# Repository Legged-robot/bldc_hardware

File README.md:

# BLDC motor controller Hardware

| Eagle PCB| Mounted PCB Controller |
:-:|:-:
 |  

## Credits
Controller based on [3phase_integrated from Ben Katz](https://github.com/bgkatz/3phase_integrated)

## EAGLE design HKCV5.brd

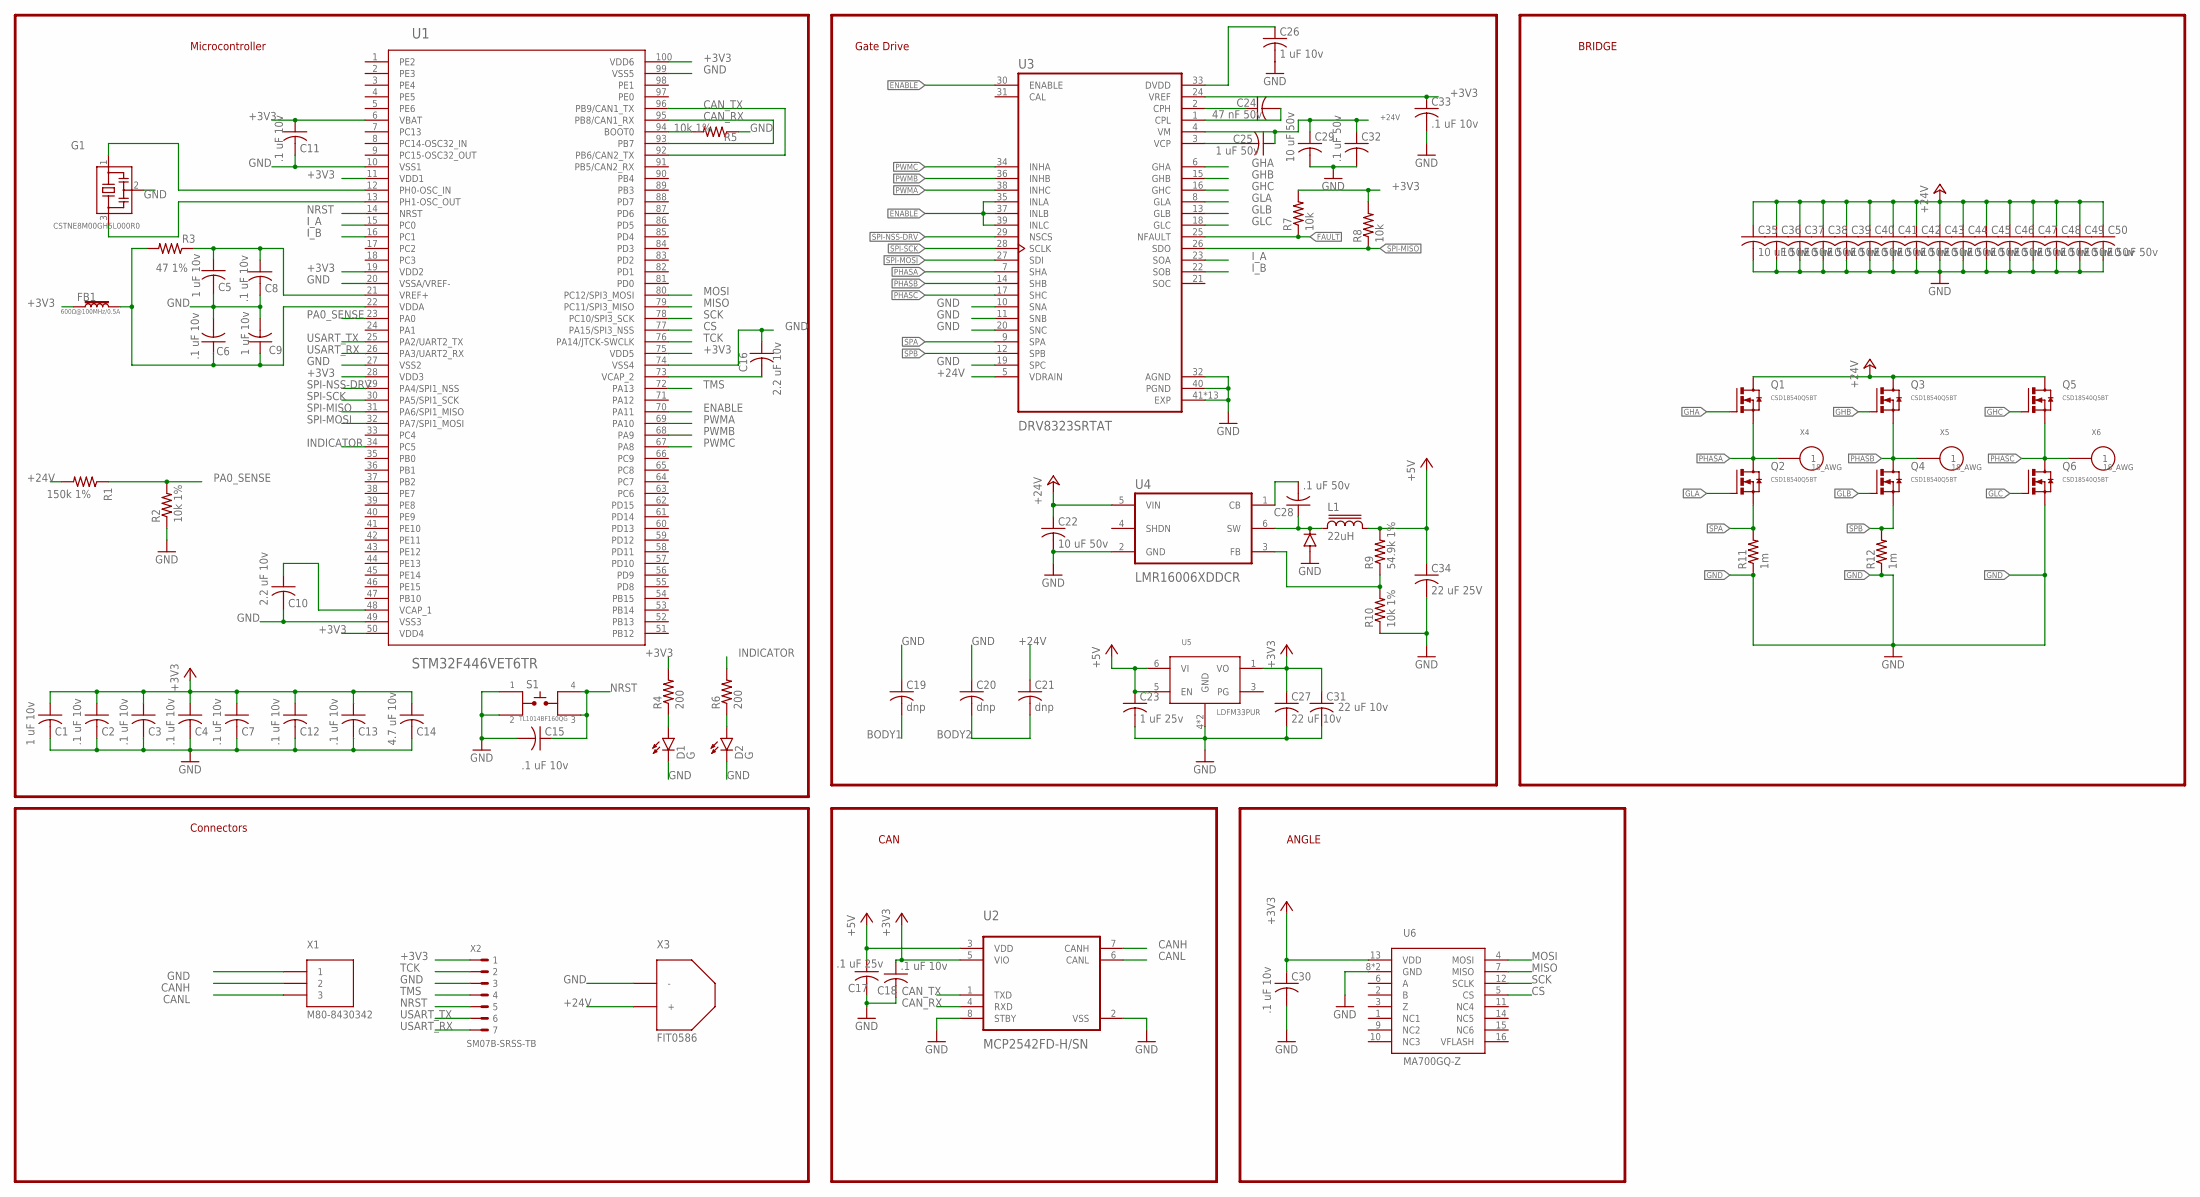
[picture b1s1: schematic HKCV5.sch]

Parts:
C1, C5, C9, C26: 1 uF 10v; C0402K
C2, C3, C4, C6, C7, C8, C11, C12, C13, C15, C18, C30, C33: .1 uF 10v; C0402K
C10, C16: 2.2 uF 10v; C0402K
C14: 4.7 uF 10v; C0402K
C17: .1 uF 25v; C0402K
C19, C20, C21: dnp; C0402K
C22, C29, C35, C36, C37, C38, C39, C40, C41, C42, C43, C44, C45, C46, C47, C48, C49, C50: 10 uF 50v; C1206K
C23: 1 uF 25v; C0402K
C24: 47 nF 50v; C0402K
C25: 1 uF 50v; C0603K
C27, C31: 22 uF 10v; C0603K
C28, C32: .1 uF 50v; C0603K
C34: 22 uF 25V; C0805K
D1, D2: G; LED-0603
D3: 500 mA 60v; SOD123
FB1: 600Ω@100MHz/0.5A; 0603
G1: CSTNE8M00GH5L000R0; CSTCE
L1: 22uH; SDR0302
Q1, Q2, Q3, Q4, Q5, Q6: CSD18540Q5BT; 8-POWERTDFN
R1: 150k 1%; R0402
R2, R5, R10: 10k 1%; R0402
R3: 47 1%; R0402
R4, R6: 200; R0402
R7, R8: 10k; R0402
R9: 54.9k 1%; R0402
R11, R12: 1m; R1210
S1: TL1014BF160QG; TL1014
U1: STM32F446VET6TR; LQFP100
U2: MCP2542FD-H/SN; 8-LEADSOIC
U3: DRV8323SRTAT; RTA-PACKAGE
U4: LMR16006XDDCR; SOT-23-6-THIN
U5: LDFM33PUR; DFN6-3X3
U6: MA700GQ-Z; QFN16
X1: M80-8430342
X2: SM07B-SRSS-TB
X3: FIT0586; XT30
X4, X5, X6: 18_AWG; 18_AWG_PAD

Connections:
+3V3: C1.1, C2.1, C3.1, C4.1, C7.1, C11.1, C12.1, C13.1, C14.1, C18.1, C27.1, C30.1, C31.1, C33.1, FB1.1, R4.2, R7.2, R8.2, U1.6 (VBAT), U1.11 (VDD1), U1.19 (VDD2), U1.28 (VDD3), U1.50 (VDD4), U1.75 (VDD5), U1.100 (VDD6), U2.5 (VIO), U3.24 (VREF), U5.1 (VO), U6.13 (VDD), X2.1
+5V: C17.1, C23.1, C34.1, L1.2, R9.2, U2.3 (VDD), U5.5 (EN), U5.6 (VI)
+24V: C21.1, C22.1, C25.1, C29.1, C32.1, C35.1, C36.1, C37.1, C38.1, C39.1, C40.1, C41.1, C42.1, C43.1, C44.1, C45.1, C46.1, C47.1, C48.1, C49.1, C50.1, Q1.5_1 (D), Q1.5_2 (D), Q1.5_3 (D), Q1.5_4 (D), Q1.5_5 (D), Q1.5_6 (D), Q1.5_7 (D), Q1.5_8 (D), Q1.5_9 (D), Q1.5_10 (D), Q1.5_11 (D), Q1.5_12 (D), Q1.5_13 (D), Q1.5_14 (D), Q1.5_15 (D), Q1.5_16 (D), Q1.5_17 (D), Q1.5_18 (D), Q1.5_19 (D), Q1.5_20 (D), Q1.5_21 (D), Q1.5_22 (D), Q1.5_23 (D), Q1.5_24 (D), Q1.5_25 (D), Q1.5_26 (D), Q1.5_27 (D), Q1.5_28 (D), Q1.5_29 (D), Q1.5_30 (D), Q3.5_1 (D), Q3.5_2 (D), Q3.5_3 (D), Q3.5_4 (D), Q3.5_5 (D), Q3.5_6 (D), Q3.5_7 (D), Q3.5_8 (D), Q3.5_9 (D), Q3.5_10 (D), Q3.5_11 (D), Q3.5_12 (D), Q3.5_13 (D), Q3.5_14 (D), Q3.5_15 (D), Q3.5_16 (D), Q3.5_17 (D), Q3.5_18 (D), Q3.5_19 (D), Q3.5_20 (D), Q3.5_21 (D), Q3.5_22 (D), Q3.5_23 (D), Q3.5_24 (D), Q3.5_25 (D), Q3.5_26 (D), Q3.5_27 (D), Q3.5_28 (D), Q3.5_29 (D), Q3.5_30 (D), Q5.5_1 (D), Q5.5_2 (D), Q5.5_3 (D), Q5.5_4 (D), Q5.5_5 (D), Q5.5_6 (D), Q5.5_7 (D), Q5.5_8 (D), Q5.5_9 (D), Q5.5_10 (D), Q5.5_11 (D), Q5.5_12 (D), Q5.5_13 (D), Q5.5_14 (D), Q5.5_15 (D), Q5.5_16 (D), Q5.5_17 (D), Q5.5_18 (D), Q5.5_19 (D), Q5.5_20 (D), Q5.5_21 (D), Q5.5_22 (D), Q5.5_23 (D), Q5.5_24 (D), Q5.5_25 (D), Q5.5_26 (D), Q5.5_27 (D), Q5.5_28 (D), Q5.5_29 (D), Q5.5_30 (D), R1.2, U3.4 (VM), U3.5 (VDRAIN), U4.5 (VIN), X3.+
BODY1: C19.2
BODY2: C20.2, C21.2
BOOT0: R5.2, U1.94 (BOOT0)
CANH: U2.7 (CANH), X1.2
CANL: U2.6 (CANL), X1.3
CAN_RX: U1.93 (PB7), U1.95 (PB8/CAN1_RX), U2.4 (RXD)
CAN_TX: U1.92 (PB6/CAN2_TX), U1.96 (PB9/CAN1_TX), U2.1 (TXD)
CB: C28.2, U4.1 (CB)
CPH: C24.1, U3.2 (CPH)
CPL: C24.2, U3.1 (CPL)
CS: U1.77 (PA15/SPI3_NSS), U6.5 (CS)
D1: D1.A, R4.1
D2: D2.A, R6.1
DVDD: C26.1, U3.33 (DVDD)
ENABLE: U1.70 (PA11), U3.30 (ENABLE), U3.35 (INLA), U3.37 (INLB), U3.39 (INLC)
FAULT: R7.1, U3.25 (NFAULT)
FB: R9.1, R10.2, U4.3 (FB)
GHA: Q1.4 (G), U3.6 (GHA)
GHB: Q3.4 (G), U3.15 (GHB)
GHC: Q5.4 (G), U3.16 (GHC)
GLA: Q2.4 (G), U3.8 (GLA)
GLB: Q4.4 (G), U3.13 (GLB)
GLC: Q6.4 (G), U3.18 (GLC)
GND: C1.2, C2.2, C3.2, C4.2, C5.2, C6.2, C7.2, C8.2, C9.2, C10.2, C11.2, C12.2, C13.2, C14.2, C15.2, C16.1, C17.2, C18.2, C19.1, C20.1, C22.2, C23.2, C26.2, C27.2, C29.2, C30.2, C31.2, C32.2, C33.2, C34.2, C35.2, C36.2, C37.2, C38.2, C39.2, C40.2, C41.2, C42.2, C43.2, C44.2, C45.2, C46.2, C47.2, C48.2, C49.2, C50.2, D1.C, D2.C, D3.A, G1.2, Q6.1 (S), Q6.2 (S), Q6.3 (S), R2.1, R5.1, R10.1, R11.1, R12.1, S1.1, S1.2, U1.10 (VSS1), U1.20 (VSSA/VREF-), U1.27 (VSS2), U1.49 (VSS3), U1.74 (VSS4), U1.99 (VSS5), U2.2 (VSS), U2.8 (STBY), U3.10 (SNA), U3.11 (SNB), U3.19 (SPC), U3.20 (SNC), U3.32 (AGND), U3.40 (PGND), U3.41 (EXP), U3.41_1 (EXP), U3.41_2 (EXP), U3.41_3 (EXP), U3.41_4 (EXP), U3.41_5 (EXP), U3.41_6 (EXP), U3.41_7 (EXP), U3.41_8 (EXP), U3.41_9 (EXP), U3.41_10 (EXP), U3.41_11 (EXP), U3.41_12 (EXP), U4.2 (GND), U5.4 (GND), U5.EXP (GND), U6.8 (GND), U6.TH (GND), X1.1, X2.3, X3.-
INDICATOR: R6.2, U1.34 (PC5)
I_A: U1.15 (PC0), U3.23 (SOA)
I_B: U1.16 (PC1), U3.22 (SOB)
MISO: U1.79 (PC11/SPI3_MISO), U6.7 (MISO)
MOSI: U1.80 (PC12/SPI3_MOSI), U6.4 (MOSI)
NRST: C15.1, S1.3, S1.4, U1.14 (NRST), X2.5
OSC_IN: G1.1, U1.12 (PH0-OSC_IN)
OSC_OUT: G1.3, U1.13 (PH1-OSC_OUT)
PA0_SENSE: R1.1, R2.2, U1.23 (PA0)
PHASA: Q1.1 (S), Q1.2 (S), Q1.3 (S), Q2.5_1 (D), Q2.5_2 (D), Q2.5_3 (D), Q2.5_4 (D), Q2.5_5 (D), Q2.5_6 (D), Q2.5_7 (D), Q2.5_8 (D), Q2.5_9 (D), Q2.5_10 (D), Q2.5_11 (D), Q2.5_12 (D), Q2.5_13 (D), Q2.5_14 (D), Q2.5_15 (D), Q2.5_16 (D), Q2.5_17 (D), Q2.5_18 (D), Q2.5_19 (D), Q2.5_20 (D), Q2.5_21 (D), Q2.5_22 (D), Q2.5_23 (D), Q2.5_24 (D), Q2.5_25 (D), Q2.5_26 (D), Q2.5_27 (D), Q2.5_28 (D), Q2.5_29 (D), Q2.5_30 (D), U3.7 (SHA), X4.1
PHASB: Q3.1 (S), Q3.2 (S), Q3.3 (S), Q4.5_1 (D), Q4.5_2 (D), Q4.5_3 (D), Q4.5_4 (D), Q4.5_5 (D), Q4.5_6 (D), Q4.5_7 (D), Q4.5_8 (D), Q4.5_9 (D), Q4.5_10 (D), Q4.5_11 (D), Q4.5_12 (D), Q4.5_13 (D), Q4.5_14 (D), Q4.5_15 (D), Q4.5_16 (D), Q4.5_17 (D), Q4.5_18 (D), Q4.5_19 (D), Q4.5_20 (D), Q4.5_21 (D), Q4.5_22 (D), Q4.5_23 (D), Q4.5_24 (D), Q4.5_25 (D), Q4.5_26 (D), Q4.5_27 (D), Q4.5_28 (D), Q4.5_29 (D), Q4.5_30 (D), U3.14 (SHB), X5.1
PHASC: Q5.1 (S), Q5.2 (S), Q5.3 (S), Q6.5_1 (D), Q6.5_2 (D), Q6.5_3 (D), Q6.5_4 (D), Q6.5_5 (D), Q6.5_6 (D), Q6.5_7 (D), Q6.5_8 (D), Q6.5_9 (D), Q6.5_10 (D), Q6.5_11 (D), Q6.5_12 (D), Q6.5_13 (D), Q6.5_14 (D), Q6.5_15 (D), Q6.5_16 (D), Q6.5_17 (D), Q6.5_18 (D), Q6.5_19 (D), Q6.5_20 (D), Q6.5_21 (D), Q6.5_22 (D), Q6.5_23 (D), Q6.5_24 (D), Q6.5_25 (D), Q6.5_26 (D), Q6.5_27 (D), Q6.5_28 (D), Q6.5_29 (D), Q6.5_30 (D), U3.17 (SHC), X6.1
PWMA: U1.69 (PA10), U3.38 (INHC)
PWMB: U1.68 (PA9), U3.36 (INHB)
PWMC: U1.67 (PA8), U3.34 (INHA)
SCK: U1.78 (PC10/SPI3_SCK), U6.12 (SCLK)
SPA: Q2.1 (S), Q2.2 (S), Q2.3 (S), R11.2, U3.9 (SPA)
SPB: Q4.1 (S), Q4.2 (S), Q4.3 (S), R12.2, U3.12 (SPB)
SPI-MISO: R8.1, U1.31 (PA6/SPI1_MISO), U3.26 (SDO)
SPI-MOSI: U1.32 (PA7/SPI1_MOSI), U3.27 (SDI)
SPI-NSS-DRV: U1.29 (PA4/SPI1_NSS), U3.29 (NSCS)
SPI-SCK: U1.30 (PA5/SPI1_SCK), U3.28 (SCLK)
SW: C28.1, D3.C, L1.1, U4.6 (SW)
TCK: U1.76 (PA14/JTCK-SWCLK), X2.2
TMS: U1.72 (PA13), X2.4
USART_RX: U1.26 (PA3/UART2_RX), X2.7
USART_TX: U1.25 (PA2/UART2_TX), X2.6
VCAP_1: C10.1, U1.48 (VCAP_1)
VCAP_2: C16.2, U1.73 (VCAP_2)
VCP: C25.2, U3.3 (VCP)
VDDA: C6.1, C9.1, FB1.2, R3.2, U1.22 (VDDA)
VREF+: C5.1, C8.1, R3.1, U1.21 (VREF+)

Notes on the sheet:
Gate Drive
Microcontroller
CAN
Connectors
ANGLE
BRIDGE

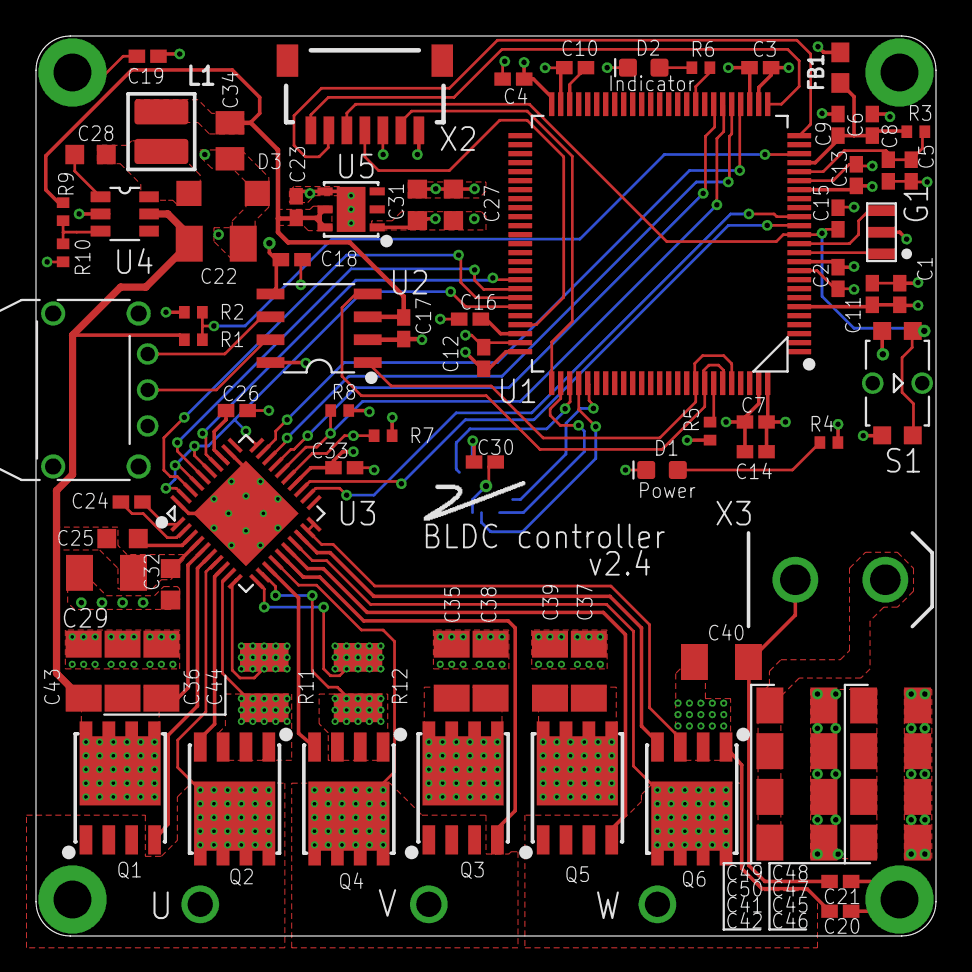
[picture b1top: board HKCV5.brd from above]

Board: 4 copper layers, 50.0 x 50.0 mm, 87 parts (1 on the bottom side), 58 nets.

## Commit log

2021-04-01 HKC Integrated V2.2 from Ben Katz
2021-04-05 Ignore history files. Board Pictures
2021-04-05 Eagle project files
2021-04-20 v2.3 Ready for review
2021-04-22 CAP rated voltage increase, BOM
2021-04-29 Pre-final - board sent to JLCPCB on review
2021-12-26 Mistakes discovered after using PCB

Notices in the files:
parts and their libraries:
SparkFun-LED: Licensing: Creative Commons ShareAlike 4.0 International - https://creativecommons.org/licenses/by-sa/4.0
inductor-bourns: Copyright (C) 2008, Bob Starr
